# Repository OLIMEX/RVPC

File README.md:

# RVPC
The EURO 1.00 Risc-V personal computer with VGA and Keyboard and Woz like monitor. The purpose of this project is to make educational platform which people can use to learn RISCV assembler and experiment like in the old days in 1980s :)

https://www.olimex.com/Products/Retro-Computers/RVPC/open-source-hardware

## Licensee
* Hardware is released under CERN Open Hardware Licence Version 2 - Strongly Reciprocal
* Software is released under GPL V3 Licensee
* Documentation is released under CC BY-SA 4.0

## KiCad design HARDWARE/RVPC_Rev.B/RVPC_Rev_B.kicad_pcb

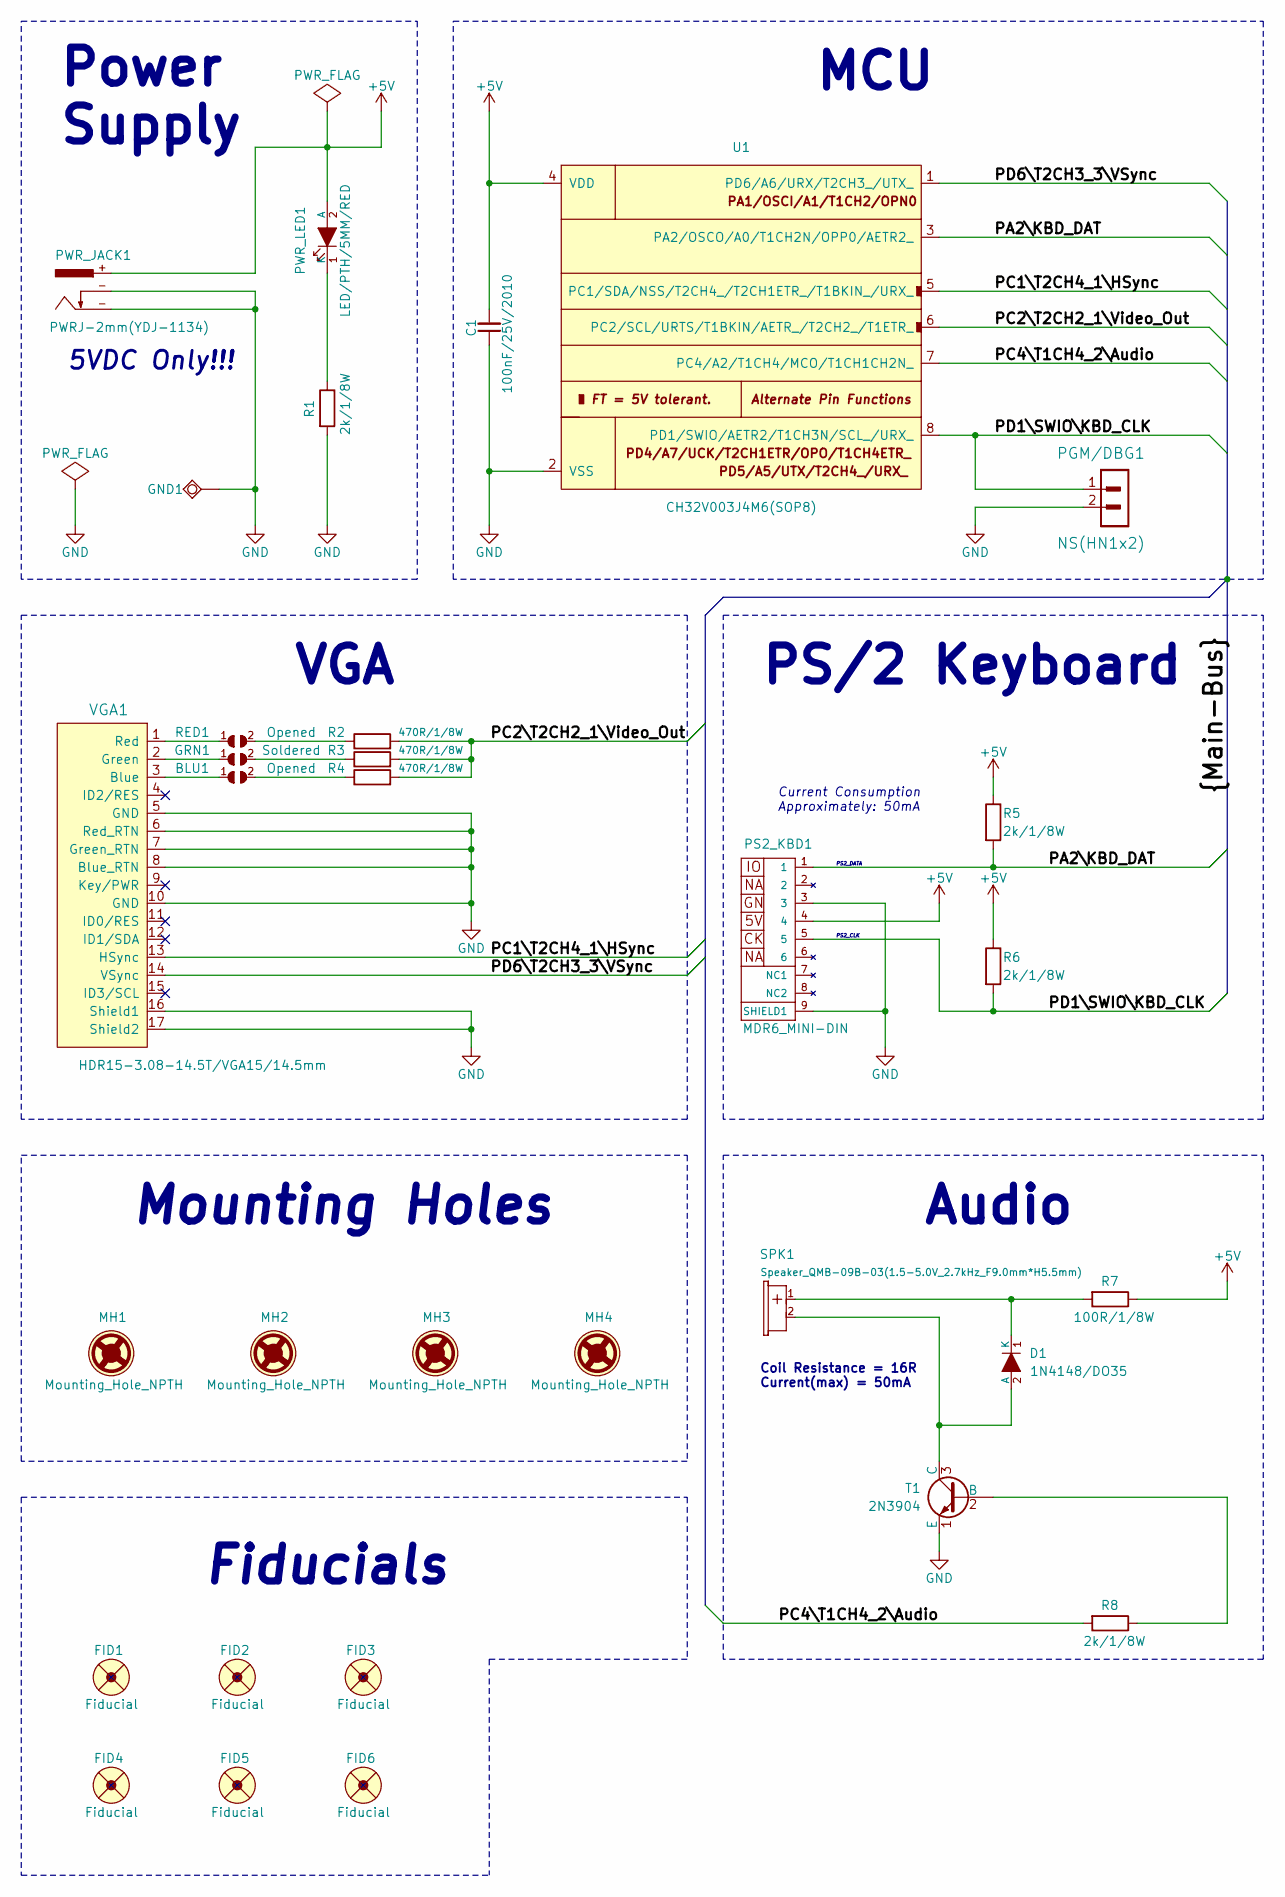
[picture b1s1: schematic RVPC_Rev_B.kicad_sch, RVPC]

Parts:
BLU1: Opened; SJ_1_SMALLER
C1: 100nF/25V/2010; C2010
D1: 1N4148/DO35; DO35_1K_2A
FID1, FID2, FID3: Fiducial; Fiducial1x3
FID4, FID5, FID6: Fiducial; Fiducial1x3_Paste
GND1: TESTPAD; TEST_PAD40x70_SQUARE
GRN1: Soldered; SJ_1_SMALLER
MH1, MH2, MH3, MH4: Mounting_Hole_NPTH; Mounting_Hole_Drill-3.3mm_Clerance-7mm
PGM/DBG1: NS(HN1x2); HN1x2
PS2_KBD1: MDR6_MINI-DIN; PS2_MDR6_MINI-DIN
PWR_JACK1: PWRJ-2mm(YDJ-1134); PWRJ-2mm(YDJ-1136)
PWR_LED1: LED/PTH/5MM/RED; LED-5mm-PTH-KA
R1, R5, R6, R8: 2k/1/8W; R_0.125W_PTH
R2, R3, R4: 470R/1/8W; R_0.125W_PTH
R7: 100R/1/8W; R_0.125W_PTH
RED1: Opened; SJ_1_SMALLER
SPK1: Speaker_QMB-09B-03(1.5-5.0V_2.7kHz_F9.0mm*H5.5mm); Speaker_QMB-09B-03_1-Plus_2-Minus
T1: 2N3904; TO-92_PTH
U1: CH32V003J4M6(SOP8); SOIC-8_150mil
VGA1: HDR15-3.08-14.5T/VGA15/14.5mm; VGA15-F(HDR15-3.08-14.5T)_DrillSlot

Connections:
+5V: C1.2, PS2_KBD1.4, PWR_JACK1.+, PWR_LED1.2 (A), R5.1, R6.1, R7.1, U1.4 (VDD)
/PA2\KBD_DAT: PS2_KBD1.1, R5.2, U1.3 (PA2/OSCO/A0/T1CH2N/OPP0/AETR2_)
/PC1\T2CH4_1\HSync: U1.5 (PC1/SDA/NSS/T2CH4_/T2CH1ETR_/T1BKIN_/UR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), VGA1.13 (HSync)
/PC2\T2CH2_1\Video_Out: R2.2, R3.2, R4.2, U1.6 (PC2/SCL/URTS/T1BKIN/AETR_/T2CH2_/T1ETR_)
/PC4\T1CH4_2\Audio: R8.2, U1.7 (PC4/A2/T1CH4/MCO/T1CH1CH2N_)
/PD1\SWIO\KBD_CLK: PGM/DBG1.1, PS2_KBD1.5, R6.2, U1.8 (PD1/SWIO/AETR2/T1CH3N/SCL_/URX_)
/PD6\T2CH3_3\VSync: U1.1 (PD6/A6/URX/T2CH3_/UTX_), VGA1.14 (VSync)
GND: C1.1, GND1.1 (Pad), PGM/DBG1.2, PS2_KBD1.3, PS2_KBD1.9 (SHIELD1), PWR_JACK1.-, R1.2, T1.1 (E), U1.2 (VSS), VGA1.5 (GND), VGA1.6 (Red_RTN), VGA1.7 (Green_RTN), VGA1.8 (Blue_RTN), VGA1.10 (GND), VGA1.16 (Shield1), VGA1.17 (Shield2)
unnamed: BLU1.2, R4.1
unnamed: D1.2 (A), SPK1.2 (MINUS), T1.3 (C)
unnamed: D1.1 (K), R7.2, SPK1.1 (PLUS)
unnamed: GRN1.2, R3.1
unnamed: PWR_LED1.1 (K), R1.1
unnamed: R2.1, RED1.2
unnamed: R8.1, T1.2 (B)
unnamed: BLU1.1, VGA1.3 (Blue)
unnamed: GRN1.1, VGA1.2 (Green)
unnamed: RED1.1, VGA1.1 (Red)

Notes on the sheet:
Power Supply
5VDC Only!!!
Mounting Holes
PS/2 Keyboard
PS2_CLK
Current Consumption Approximately: 50mA
MCU
PS2_DATA
VGA
Fiducials
Audio
Coil Resistance = 16R Current(max) = 50mA

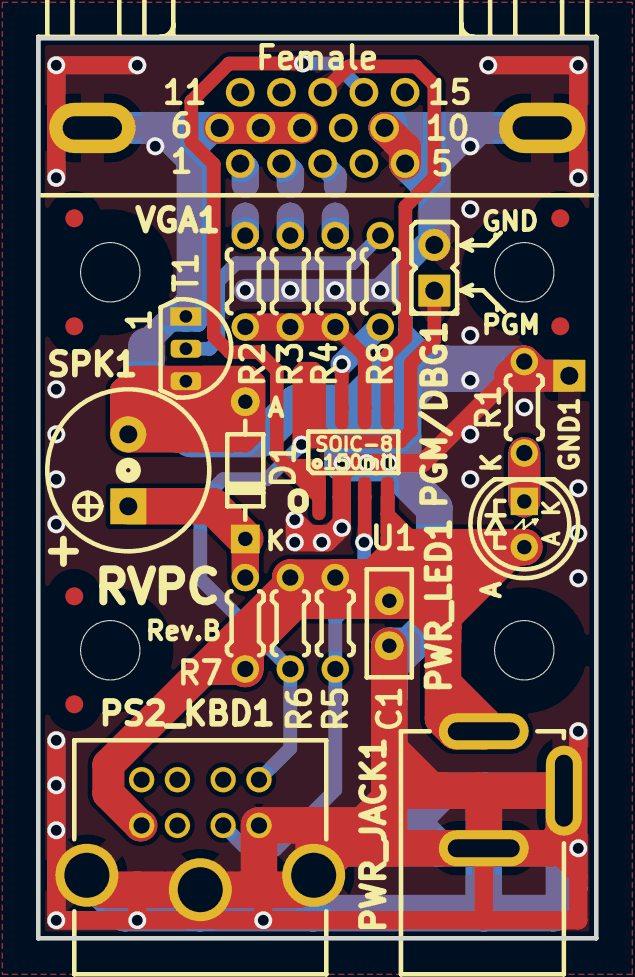
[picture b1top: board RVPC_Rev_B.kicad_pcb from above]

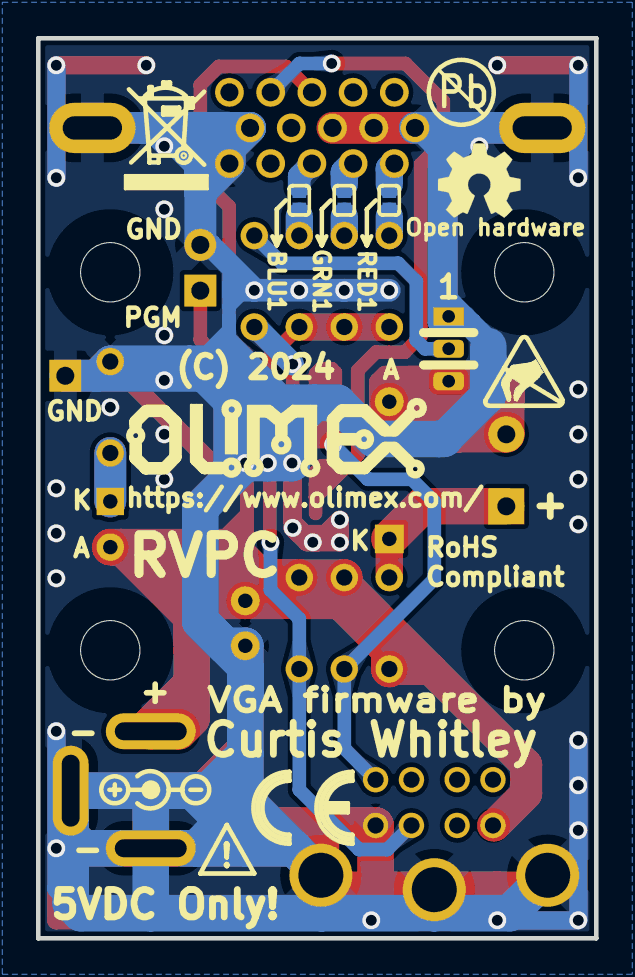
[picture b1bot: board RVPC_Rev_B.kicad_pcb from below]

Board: 2 copper layers, 31.0 x 50.0 mm, 38 parts (9 on the bottom side), 18 nets.

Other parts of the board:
Logo_OLIMEX_TB: Logo_OLIMEX_TB
Sign_Antistatic_Small: Sign_Antistatic; Sign_Antistatic_4.5mmX2.8mm
Sign_CE: CE_Sign
Sign_OSHW_7.3x6.0mm: Sign_OSHW_7.3x6.0mm; Sign_OSHW_7.3x6.0mmn
Sign_PB-Free: Sign_PB-Free
Sign_RecycleBin_1: Sign_RecycleBin_1

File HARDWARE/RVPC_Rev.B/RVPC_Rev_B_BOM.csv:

Quantity,Value,Footprint,Reference
1,100nF/25V/2010,C2010,C1
1,1N4148/DO35,DO35_1K_2A,D1
1,HN1x2,HN1x2,PGM/DBG1
1,MDR6_MINI-DIN,PS2_MDR6_MINI-DIN,PS2_KBD1
1,PWRJ-2mm(YDJ-1134),PWRJ-2mm(YDJ-1136),PWR_JACK1
1,LED/PTH/5MM/RED,LED-5mm-PTH-KA,PWR_LED1
4,2k/1/8W,R_0.125W_PTH,"R1, R5, R6, R8"
3,470R/1/8W,R_0.125W_PTH,"R2, R3, R4"
1,100R/1/8W,R_0.125W_PTH,R7
1,Speaker_QMB-09B-03(1.5-5.0V_2.7kHz_F9.0mm*H5.5mm),Speaker_QMB-09B-03_1-Plus_2-Minus,SPK1
1,2N3904,TO-92_PTH,T1
1,CH32V003J4M6(SOP8),SOIC-8_150mil,U1
1,HDR15-3.08-14.5T/VGA15/14.5mm,VGA15-F(HDR15-3.08-14.5T)_DrillSlot,VGA1

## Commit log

2024-05-30 initial upload schematic and CAD files
2024-06-27 update user manual and demo
2024-07-03 update user manual
2024-07-06 Add .gitignore
2024-07-06 Add PicoRVD instructions to user manual
2024-07-10 update vga project
2024-09-26 update demo code
2024-10-02 update RVPC software
2024-10-31 update assembly instructions
2024-11-01 Removed links
2024-11-01 Added sources
2024-11-01 Update manual
2024-11-01 Added prebuilt binaries
2024-11-04 A small correction in SOFTWARE/README.md
    Correct the reference to the `rvpc` directory and clean up the language a bit.
2024-11-06 use 1/4th of flash for character definitions
    This works because for CH32v003 you can just set BR all the time and
    have BS determine the full state of a GPIO in the BSHR register.
    According to 7.3.1.4 of CH32V003RM:
    If both BR and BS bits are set, the BS bit takes effect.
    This moves some extra work to vga_prepare_line.
2025-07-29 Fix typo
2025-08-12 Compile all examples in CI
2026-01-29 Fix grammar and clarity in README.md

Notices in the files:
HARDWARE/RVPC_Rev.B/RVPC_Rev_B.kicad_pcb:
(C) 2024
